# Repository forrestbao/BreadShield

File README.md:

# BreadShield

BreadShield is a shield that maps Arduino pins to breadboard ties without jumper wires. It inserts into both of them, firmly bridging them together mechanically and electrically.

Watch [this video](https://www.youtube.com/watch?v=qSHss7gq7b0) to see BreadShield in action! 

To order, scroll down to see our distributors. 

# Why

Many projects start with connecting an Arduino and a breadboard using jumper wires. But jumper wires can easily become too many to manage, forming a mess of spaghetti that is difficult to trace, debug, and swap: 

#Introducing BreadShield: The Arduino shield for breadboards

Like you, we have suffered enough. One day we asked, what if all of those messy jumper wires could become one shield? So BreadShield was born. With BreadShield, the messy project above can be simplified into: 

# BreadShield vs. jumper wires

# No more choosing between shields or breadboards

Before, you cannot use shields together with breadboards because the jumper wires occupy sockets for shields. No more! With BreadShield, you can use both, simultaneously:

# Pinout of Breadshield

# Organization of files in the repo
* KiCAD: the KiCAD files of the PCB
* demo: programs and documentations for demos
* images: some images of BreadShield

# License
BreadShield (c) by Forrest Sheng Bao et al.

BreadShield is licensed under a
Creative Commons Attribution-ShareAlike 4.0 International License.

You should have received a copy of the license along with this
work. If not, see <http://creativecommons.org/licenses/by-sa/4.0/>.

A copy of this license is in the file `license.md`.

# Where to buy
* [Tindie, by the author himself](https://www.tindie.com/products/edit/breadshield/) 
* [ARMWorks, 1 or 3-pack](https://andahammer.com/index.php?route=product/product&path=68&product_id=299)
* [Mouser](https://www.mouser.com/Search/Refine?FS=TRUE&N=4246651945+4292906361)
* [Crowd Supply](https://www.crowdsupply.com/loser/breadshield)

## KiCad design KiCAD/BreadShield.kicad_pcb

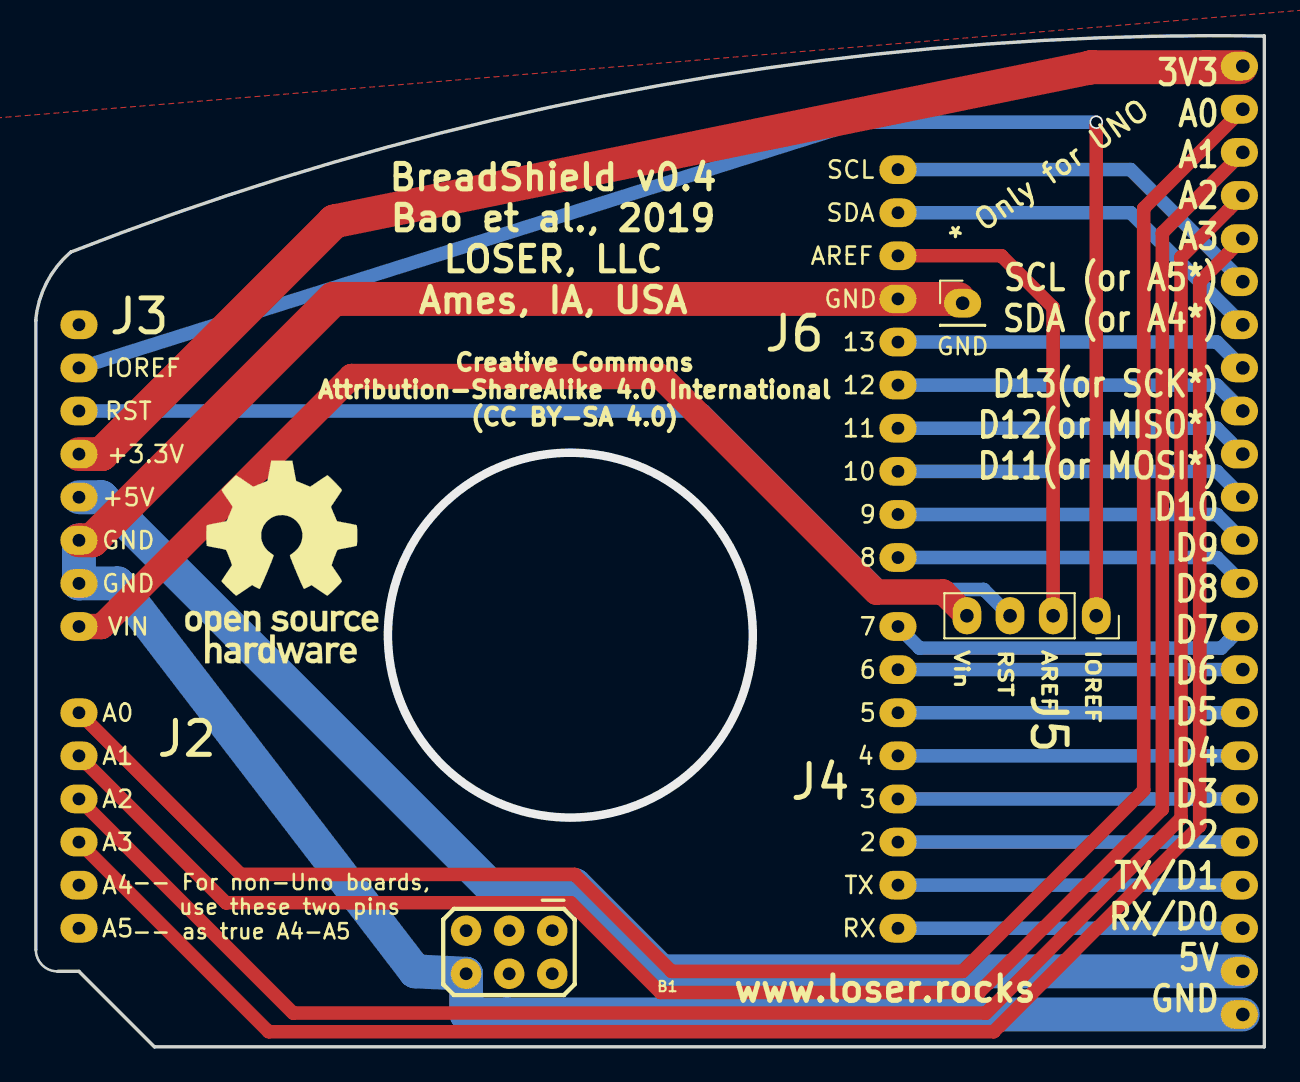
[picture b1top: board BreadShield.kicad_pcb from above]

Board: 2 copper layers, 72.4 x 59.6 mm, 4 parts (1 on the bottom side), 27 nets.

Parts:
B1: ARDUINO_UNO_R3_SHIELD_ICSP; UNO_R3_SHIELD_ICSP
GND: PinHeader_1x01_P2.54mm_Vertical
J1: Conn_01x23_Male; PinHeader_1x23_P2.54mm_Vertical
J5: Conn_01x04_Female; PinSocket_1x04_P2.54mm_Vertical

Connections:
/3V3: B1.3.3V, J1.23
/5V: B1.5V, J1.2
/A0: B1.A0, J1.22
/A1: B1.A1, J1.21
/A2: B1.A2, J1.20
/A3: B1.A3, J1.19
/AREF: B1.AREF, J5.2
/D2: B1.D2, J1.5
/D3: B1.D3, J1.6
/D4: B1.D4, J1.7
/D5: B1.D5, J1.8
/D6: B1.D6, J1.9
/D7: B1.D7, J1.10
/D8: B1.D8, J1.11
/D9: B1.D9, J1.12
/D10: B1.D10, J1.13
/GND: B1.GND@, B1.GND_, GND.1, J1.1
/IOREF: B1.IORE, J5.1
/MISO_D12: B1.D12, J1.15
/MOSI_D11: B1.D11, J1.14
/RES: B1.RES, J5.3
/RX: B1.RX, J1.3
/SCK_D13: B1.D13, J1.16
/SCL_A5: B1.SCL, J1.18
/SDA_A4: B1.SDA, J1.17
/TX: B1.TX, J1.4
/Vin: B1.VIN, J5.4

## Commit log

2019-05-31 add demo files
2019-07-21 push v0.4 design file
2019-07-21 add cover image

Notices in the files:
KiCAD/BreadShield.kicad_pcb:
(CC BY-SA 4.0)
